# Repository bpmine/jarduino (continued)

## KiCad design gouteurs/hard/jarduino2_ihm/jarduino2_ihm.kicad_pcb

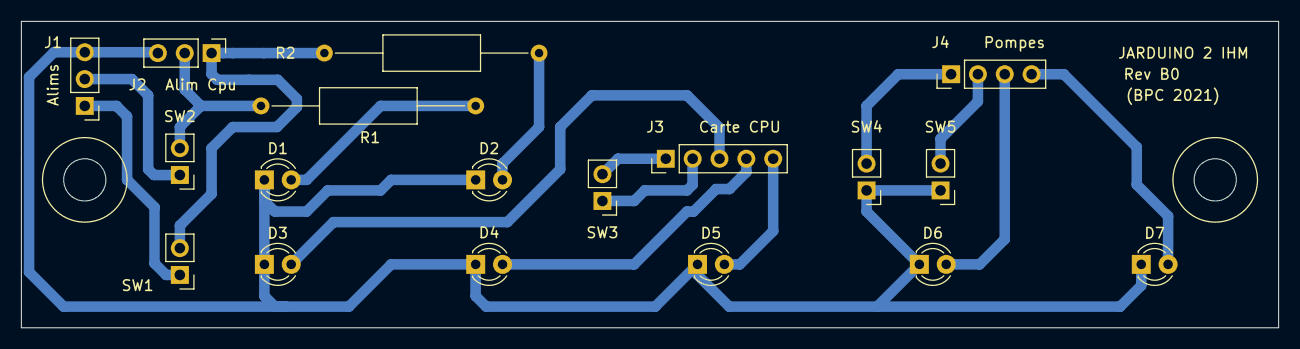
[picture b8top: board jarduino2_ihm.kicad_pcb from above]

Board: 2 copper layers, 119.0 x 29.0 mm, 18 parts (0 on the bottom side), 16 nets.

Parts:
D1: Solaire OK; LED_D3.0mm_Clear
D2: Batterie OK; LED_D3.0mm_Clear
D3: Solaire; LED_D3.0mm_Clear
D4: Power/Batt; LED_D3.0mm_Clear
D5: Piles; LED_D3.0mm_Clear
D6: Pompe 1; LED_D3.0mm_Clear
D7: Pompe 2; LED_D3.0mm_Clear
J1, J2: Alim CPU; PinHeader_1x03_P2.54mm_Vertical
J3: Indicateurs; PinHeader_1x05_P2.54mm_Vertical
J4: Pompes; PinHeader_1x04_P2.54mm_Vertical
R1, R2: 1k; R_Axial_DIN0309_L9.0mm_D3.2mm_P20.32mm_Horizontal
SW1: Batterie On/Off; PinHeader_1x02_P2.54mm_Vertical
SW2: Solaire ON/OFF; PinHeader_1x02_P2.54mm_Vertical
SW3: Pile On/Off; PinHeader_1x02_P2.54mm_Vertical
SW4: Pompe 1; PinHeader_1x02_P2.54mm_Vertical
SW5: Pompe 2; PinHeader_1x02_P2.54mm_Vertical

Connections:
GND: D1.1, D2.1, D3.1, D4.1, D5.1, D6.1, D7.1, J1.3, J2.3, SW4.1, SW5.1
unnamed: D1.2, R1.1
unnamed: D2.2, R2.1
unnamed: D3.2, J3.3
unnamed: D4.2, J3.4
unnamed: D5.2, J3.5
unnamed: D6.2, J4.3
unnamed: D7.2, J4.4
unnamed: J1.1, SW1.1
unnamed: J1.2, SW2.1
unnamed: J2.1, R2.2, SW1.2
unnamed: J2.2, R1.2, SW2.2
unnamed: J3.1, SW3.2
unnamed: J3.2, SW3.1
unnamed: J4.1, SW4.2
unnamed: J4.2, SW5.2

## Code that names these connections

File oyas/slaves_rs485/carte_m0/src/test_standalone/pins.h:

#ifndef PINS_HEADER_INCLUDED
#define PINS_HEADER_INCLUDED

/// Port 3
#define PIN_CPT_LVL_LOW   PA15
#define PIN_CPT_LVL_HIGH  PA14
#define PIN_CMD_EV        PA04
#define PIN_TX_EN         PA18
#define PIN_UART_TX		  PA16
#define PIN_UART_RX       PA17
#define GPIO_PMUX_SERCOM  GPIO_PMUX_C

/// Port 2
#define PIN_MES_V         PA02
#define PIN_MES_V_ADC_MUXPOS    0  
#define PIN_LED1          PA20

/// Port 1
#define PIN_ADDR_A1       PA23
#define PIN_ADDR_A2       PA25
#define PIN_ADDR_A3       PA22
#define PIN_ADDR_A4       PA24

#endif

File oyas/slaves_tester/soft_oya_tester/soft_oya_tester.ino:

/**
 * @file soft_oya_tester.ino
 * 
 * @brief Testeur d'Oyas
 * 
 * Ce programme se comporte comme un maître RS485
 *   - Il envoie périodiquement:
 *      - Une trame de commande avec l'adresse de l'esclave sélectionné
 *      - une trame de sync (adresse 'S')
 *      
 *   - Lorsque le bouton FIRE est presse, alors la commande déclenche l'EV de l'OYA/POMPE correspondant à l'adresse sélectionnée
 *   - Les deux LEDs indiquent le niveau ou le débit selon si l'esclave a l'adresse 1 (pompe) ou non
 *   - Le bouton ADDRESS permet de changer l'adresse sélectionnée
*/
#include <EEPROM.h>

#include "timer.h"
#include "prot.h"
#include "frames.hpp"
#include "framebuilder.h"

#define SEG_A     (8)  /// Pin 8
#define SEG_B     (9)  /// Pin 9
#define SEG_C     (3)  /// Pin 3
#define SEG_D     (4)  /// Pin 4
#define SEG_E     (5)  /// Pin 5
#define SEG_F     (7)  /// Pin 7
#define SEG_G     (6)  /// Pin 6
#define SEG_DP    (2)  /// Pin 2

#define FIRE      (A5)
#define ADDRESS   (11)

#define LD_LEFT   (A2)
#define LD_RIGHT  (A1)

#define TX_EN     (10)

#define NB_SEGS (8)
const int list_segs[NB_SEGS]=
{
  SEG_A,
  SEG_B,
  SEG_C,
  SEG_D,
  SEG_E,
  SEG_F,
  SEG_G,
  SEG_DP
};

#define BIT_A   (0x01)
#define BIT_B   (0x02)
#define BIT_C   (0x04)
#define BIT_D   (0x08)
#define BIT_E   (0x10)
#define BIT_F   (0x20)
#define BIT_G   (0x40)
#define BIT_DP  (0x80)

unsigned char g_addr=1;
unsigned long t0_fire_ms=0;
bool g_on=false;
bool g_low=false;
bool g_high=false;

FrameBuilder builderTX;
Timer tmrCycle(500UL,false);
Timer tmrInput(250UL,false);
Timer tmrNoComm(5000UL);

FrameBuilder builderRX;

class FrameReceiver: public IFrameReceiver
{
public:
   bool OnFrameReceive(FramePump *pump) override
   {
    g_high=false;
    g_low=false;
    tmrNoComm.start();
    return true;
   }
   
   bool OnFrameReceive(FrameOya *oya) override
   {
    g_high=oya->high();
    g_low=oya->low();
    tmrNoComm.start();
    return true;
   }
};

FrameReceiver receiver;


void display(char val,bool dp)
{
  unsigned char ret=0;
  
  switch (val)
  {
    case '0':ret=0x3F;break;
    case '1':ret=BIT_B|BIT_C;break;
    case '2':ret=BIT_A|BIT_B|BIT_G|BIT_E|BIT_D;break;
    case '3':ret=BIT_A|BIT_B|BIT_C|BIT_D|BIT_G;break;
    case '4':ret=BIT_B|BIT_C|BIT_F|BIT_G;break;
    case '5':ret=BIT_A|BIT_F|BIT_G|BIT_C|BIT_D;break;
    case '6':ret=BIT_A|BIT_C|BIT_D|BIT_E|BIT_F|BIT_G;break;
    case '7':ret=BIT_A|BIT_B|BIT_C;break;
    case '8':ret=0x7F;break;
    case '9':ret=BIT_A|BIT_B|BIT_C|BIT_D|BIT_F|BIT_G;break;
    case 'A':ret=BIT_A|BIT_B|BIT_C|BIT_E|BIT_F|BIT_G;break;    
    case 'B':ret=BIT_C|BIT_D|BIT_E|BIT_F|BIT_G;break;
    case 'C':ret=BIT_A|BIT_D|BIT_E|BIT_F;break;
    case 'D':ret=BIT_B|BIT_C|BIT_D|BIT_E|BIT_G;break;
    case 'E':ret=BIT_A|BIT_D|BIT_E|BIT_F|BIT_G;break;
    case 'F':ret=BIT_A|BIT_E|BIT_F|BIT_G;break;
    default:ret=0;break;
  }

  if (dp)
    ret|=BIT_DP;

  for (int i=0;i<NB_SEGS;i++)
  {
    if ( ( ret & (1<<i) ) == (1<<i) )
    {
      digitalWrite(list_segs[i],HIGH);
    }
    else
    {
      digitalWrite(list_segs[i],LOW);
    }
  }
}

void display_hex(unsigned char val,bool dp)
{
  if ( ( val>0) && (val<=15) )
  {
    char c;
    
    if (val<10)
      c='0'+val;
    else
      c='A'+val-10;

    display(c,dp);
  }
  else
  {
    display(0,dp);
  }
}

void setup() 
{
  Serial.begin(9600);
  for (int i=0;i<NB_SEGS;i++)
  {
    pinMode(list_segs[i],OUTPUT);
    digitalWrite(list_segs[i],LOW);
  }

  t0_fire_ms=0;
  g_addr=EEPROM.read(0);
  if ( (g_addr<1) || (g_addr>15) )
    g_addr=1;
  
  pinMode(ADDRESS,INPUT_PULLUP);
  pinMode(FIRE,INPUT_PULLUP);
    
  pinMode(LD_RIGHT,OUTPUT);
  digitalWrite(LD_RIGHT,LOW);
  
  pinMode(LD_LEFT,OUTPUT);
  digitalWrite(LD_LEFT,LOW);
  
  pinMode(TX_EN,OUTPUT);
  digitalWrite(TX_EN,LOW);

  display(0,false);  
  
  g_on=false;  

  tmrCycle.start();
  tmrInput.start();
  tmrNoComm.start();
  
  builderRX.setReceiver(&receiver);
}

int g_sendSync=false;

void sendCommandFrame(unsigned char addr)
{
  unsigned short cmds=0;
  if (g_on==true)
  {
    cmds|=(0x01<<g_addr);
  }
  
  FrameCmd cmd(cmds,addr);
  unsigned char *pMsg=builderTX.build(&cmd);

  digitalWrite(TX_EN,HIGH);
  delay(2);
  Serial.write(pMsg,builderTX.size());
  Serial.flush();
  delay(1);
  digitalWrite(TX_EN,LOW);
}

void serialEvent()
{
  while (Serial.available() > 0)
  {
    unsigned char c = Serial.read();
    builderRX.recv(c);
  }
}

void loop()
{
  bool addr=digitalRead(ADDRESS)==HIGH?false:true;
  bool fire=digitalRead(FIRE)==HIGH?false:true;
  delay(1);
  addr=addr && (digitalRead(ADDRESS)==HIGH?false:true);
  fire=fire && (digitalRead(FIRE)==HIGH?false:true);

  if (tmrInput.tick()==true)
  {
    if (addr)
    {
      g_addr++;
      if (g_addr>15)
        g_addr=1;
  
      EEPROM.write(0,g_addr);
    }
  }

  if (fire)
    g_on=true;
  else
    g_on=false;
    
  display_hex(g_addr,g_on);
  
  /*if ( (blk--) < 0 )
  {
    digitalWrite(LD_LEFT,!digitalRead(LD_LEFT));
    digitalWrite(LD_RIGHT,!digitalRead(LD_RIGHT));
    blk=4;
  }*/

  if (tmrCycle.tick()==true)
  {
    if (g_sendSync==false)
    {
      sendCommandFrame(g_addr);
      g_sendSync=true;
    }
    else
    {
      sendCommandFrame(ADDR_SYNC);
      g_sendSync=false;
    }    
  }

  if (tmrNoComm.isRunning()==true)
  {
    digitalWrite(LD_LEFT,g_low==true?HIGH:LOW);
    digitalWrite(LD_RIGHT,g_high==true?HIGH:LOW);
  }
  else
  {
    digitalWrite(LD_LEFT,LOW);
    digitalWrite(LD_RIGHT,LOW);
  }
}

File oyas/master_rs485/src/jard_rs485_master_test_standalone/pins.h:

/**
 * @file pins.h
 *
 * @brief Definition des broches de la carte Master RS485
 *
 * Serial2: Wifi
 * Serial3: Log
**/
#ifndef PINS_HEADER_INCLUDED
#define PINS_HEADER_INCLUDED

#define PIN_TX_EN         (6)     ///< Activation de la ligne RS485 (Pour emettre)
#define PIN_TEST_BTN      (2)     ///< Bouton de test (pull up interne)
#define PIN_PWR_ON        (8)     ///< Commande puissance sur réseau RS485 (esclaves)
#define PIN_DATA_LEDS     (4)     ///< Commande Data des LEDs
#define PIN_PWR_LEDS      (5)     ///< Alimentation des LEDs (via pnp)
#define PIN_PWR_WIFI      (7)     ///< Alimentation module wifi (via pnp)
#define PIN_PWR_LEDS2     (9)     ///< Alimentation des LEDs (via npn)
#define PIN_PWR_WIFI2     (10)    ///< Alimentation module wifi (via npn)


#endif

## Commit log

2024-06-09 Création demo_synoptique avec un fond svg
2024-08-23 Presentation projet OYAs
2024-08-23 Import sources du maitres 485 à partir du repo d'origine (module_uino)
2024-08-23 rename
2024-08-23 Deplacement carte maitre rs485
2024-08-23 Import du projet esclave
2024-08-24 Readme des cuves
2024-08-24 Ajout carte weemos_mqtt et sources
2024-08-24 Logiciel de commande des cuves (Client PC Windows) Design des filtres (meca)
2024-08-24 Ajout projet gouteurs
2024-08-24 Recupération des schémas d'archive dans l'ancien repo
2024-08-24 Import carte Jarduino2 du repo
2024-09-28 Import du code de la Gateway Domotique (Tel qu'utilisé été 2024)
2024-10-11 Documentation Jarduino2 + simplification arbo
2025-02-16 Commentaires todo
2025-03-01 Creation carte oya à base de MSP430
2025-03-02 Réarragement du dossier
2025-03-02 Creation carte esclave à base de AT328 (à finir - Connecter power 12V mes, ...)
2025-03-02 Correction valeurs des capas du quartz
2025-03-02 Finalisation carte AT328
2025-03-02 Renommage jard_wemos
2025-04-12 Corrections sur la carte Rev A MSP430
    - Pas de pullup interne ds MSP430
    - Correction sérigraphie et empreinte connecteur de PROG
    - Décalage LED
    - Suppression de l'entrée débit
    - Empreinte des doides TVS et des capas pour être soudables à la main
    - Empreinte D12 horizontale
2025-04-12 Suite fabrication 2025 (ajout d'info)
2025-04-13 Suite aux tests (ce programme valide la carte)
2025-04-13 Vérification du nouveau design (Rev B)
2025-04-15 Finitions + Revérification
2025-04-15 Empreinte TVS
2025-04-16 Finalisation et test des règles
2025-04-18 Améliorations sur carte AT328
    - Capas en hand soldering et en 805
    - TP + gros
    - Repères composants
    - Carte moins longue
2025-05-08 Modification valeurs de composants - C10 100nF - R4 25k - C12 1µF
2025-05-08 Déplacement du projet de carte MSP430
2025-05-08 Déplacement du soft de départ pour MSP430
2025-05-08 Programme pour tester le CPU de la carte MSP430
2025-05-08 Déplacement des projets hard: Modules arduino et carte at328
2025-05-08 Déplacements programmes de test carte arduino
2025-05-08 Déplacement programme oya arduino
2025-05-08 Annotation erreurs
2025-05-08 Réamménagement des projets de cartes pour les cuves
2025-05-10 Création logiciel carte AT328
2025-05-10 Base du logiciel slave 485
2025-05-10 Faire compiler
2025-05-10 Création prog de test autonome
2025-05-10 Test ok premier Oya en standalone
2025-05-10 Report du programme oya à partir de la carte arduino de l'an passé.
2025-05-11 MAJ pendant le test des cartes
2025-05-12 Pour test standalone de la carte MSP430
    (Manque la mesure de la tension 12V en entrée)
2025-05-14 Test d'aujourd'hui. Quelques soudures mal faites... + Reset non fonctionnel => Mettre 100nF ? (Ou bien quartz nok / capas ?)
2025-05-15 Débug conversion qui plantait... Réglage conversion different entre le mode sonde (3.6v) et le mode standalone !!
2025-05-15 Mise au point soft oya
    - Reception ok
    - Reste à gérer la réponse
    - Puis mise au propre du reste (timeout, ...)
2025-05-16 Réaménagement readme
2025-05-16 Mise à jour du protocole (était encore en version initiale de 2023 !)
2025-05-16 suite...
2025-05-17 Test de l'oya sans le timer de securité réseau ni le watchdog.
2025-05-17 Candidat au premier test in situ (ds le jardin)
2025-05-26 Intégration carte MSP430 sur le réseau
2025-05-26 Modif MAX485 -> MAX3485 (3.3V)
2025-05-28 Test du maître Hard Rev B (2025)
2025-05-28 MAJ correction limitation du courant de base des pnp (Pwr Wifi et LEDs)
2025-05-29 Ajout de la nouvelle configuration du maître des Oyas (Paul / C) Déclenchement tous les jours à midi +Corr.Bugs
2025-05-29 Modification de la configuration des esclaves. TEST OK sur 6 Esclaves côté Nord.
2025-06-05 Mise en service réseau wifi du master côté Nord/Paul
2025-06-09 Test nouvelle carte maître + ajustements timings pour Barbec + ajout oyas pour réduit + report timings barbec
2025-06-14 Remplissage tous les jours à 13h Ajustage des tempos pour réduit et Paul
    Réduit mis à jour
2025-06-14 Programmation Paul et Barbec
2025-06-15 Idées version suivante
2025-06-28 Ajout d'un site pour avoir les états des cuves et des oyas
2025-06-29 Mise à jour doc 2025 (+volume des cuves erroné)
2025-07-05 Ajout des commandes des cuves
2025-11-25 Creation CAO de la carte testeur d'OYA
    On branche le tester en un point du réseau.
    On configure l'adresse à piloter à l'aide d'un bouton + 7 SEG
    On actionne ON/OFF avec un autre bouton
2025-12-12 Changement forme de la carte (boîte de dérivation)
2025-12-12 Finalisation testeur Connecteurs des interrupteurs à choisir...
2025-12-13 Finition
2025-12-13 schema
2026-01-16 Réception rev A et corrections: - Les SW étaient à 5V au lieu de GND - Idem sur le connecteur JST du SW ON/OFF - Valeur des résistances anodes du 7seg à 220 Ohms
    Passage en Rev B pour la suivante
    + Ajout su soft de départ
2026-02-18 Création d'une carte oya avec M0
    - Plus perenne que MSP430F1232
    - Pas besoin de quartz/resonateur externe
    - Compatible avec la sonde AVR ATMEGA
    - Possibilité d'une config de mesure du débit
2026-03-06 Finitions PCB
2026-03-06 Revue de carte et de routage:
    - Amélioration découplage micro (1uF 805 sur VDDCore et 100nF 603 sur les autres selon recommendation microchip)
    - R14=1k: Moins de courant dans Q1
    - R1=R2=1k: Limiter le clamp en mode débit
    - R3 NM en mode débit
    - C17=100nF pour améliorer filtrage 3.3V
    - Ajout Capa 100nF sur reset
2026-03-07 Fin de revue avec ajout d'une diode TVS 18V en entrée
2026-03-11 Logiciel pour testeur d'oya
2026-03-11 Quelques commentaires sur le schéma pour préparer la version 2027...
2026-03-11 Correction de la capacité de la cuve
2026-03-14 Changement de la forme de la carte: Boîte 85 x 85 x 55
2026-03-14 Finalisation / règles kicad...
2026-04-04 Création d'un projet pour tester le CPU: La LED clignote.
2026-04-12 Portage du programme de test standalone MSP430 vers le M0
2026-04-13 Préparation future carte Rev B (Inversion TX/RX) Programme en cours de test
2026-04-15 Amélioration pad de R10 Sortie du module adc Calibration de la mesure d'alim
2026-04-17 Changement connecteur de programmation
2026-04-17 Plan du connecteur des niveaux + montage
2026-04-18 Ajout de 2 cuves avec fonction remplissage
2026-04-26 Préparation carte future Rev B (Correction SW) Mise au point programme.
2026-05-13 Ajout des voyants
    Rouge lent: Veille
    Rouge rapide: Off
    Rouge très rapide: Booting...
    Rouge Fixe + Bleu Lent: On
    Rouge Fixe + Bleu Rapide: Au moins une pompe en route
2026-05-13 Finalisation future Rev B
    Ajout de protections sur le 12V Bus
2026-05-13 Finalisation Future Rev B
2026-05-15 Mise à jour du site avec bootstrap local + nettoyage
2026-05-15 Amélioration rendu (plus compact + icone batterie/alim) +Simu oya
2026-05-15 Amélioration (état de réveil visible sur les LEDs = LED Bleue lente 2s puis rapide 1s quand réveillés puis 250ms si une pompe ON) Affichage service cuves down
2026-05-15 Nouveau code voyants:
    -Rouge 250ms: Erreur (service down...)
    -Rouge 2S: Veille
    -Rouge 1S: Off
    -Rouge Fixe - Bleu 2S: Réveil en cours (au moins 1 module en sleep)
    -Rouge fixe - Bleu 1S: ON
    -Rouge fixe - Bleu 250ms: Au moins une pompe active
2026-05-15 Amélioration rendu mobile + ajout RSSI
2026-05-23 Evolution code maître des oyas: - Gestion des tailles d'oyas (meme principe que la config des esclaves presents) - Memorisation config esclaves - Mise à jour config possible par mqtt et par terminal
    Site Web et serveur:
    - Affichage des gros oyas
    - Amélioration affichage quand le réseau ne répond pas (pas pertinent d'avoir le récap des niveaux bas pour ces esclaves out)
2026-05-24 Mise au point + gestion remplissage en remote jusqu'au niveau + mode depannage (a tester plus tard)
2026-05-24 Gestion remplissage au niveau + correction bug (le retour ack provoque data à 0) Weemos: Meilleur timeout de sleep
2026-05-24 oyas: Ne pas effacer les objets déjà présents
2026-05-25 ATTENTION: Changement signification slaves dans le json => Correspond à la définition interne au maitre Amélioration affichage liste bigs et slaves dans le terminal Ajout prog testeur de cable (cablé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
2026-05-29 Suite MAJ firmware Barbec
2026-06-01 Debug champ rmt: Bug dans firmware (cf état wifi remote = Pas de latch des datas) Gestion on/off par module en + du on/off application Codage fonction de réparation/nettoyage EV (à tester)
2026-06-06 Ajout d'une page pour la configuration des Oyas
    -Test ok pour ajout/suppr des oyas via client.py
    -Reste à coder le reste...
